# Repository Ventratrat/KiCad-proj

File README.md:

# THIS REPO IS OUTDATED AND NO LONGER UPDATED
KiCad projects I worked on
------------------------------------
# Projects in Repository
+ Test Stand - Testing stand files for PCB used to test thrust of RC aircraft.
+ 4-Bit Adder - Schematic and PCB for a simple 4-bit adder.

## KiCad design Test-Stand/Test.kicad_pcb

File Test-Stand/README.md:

# Overview
This folder contains most of, if not all, of the files used for a chip designed to test the voltage and current of an RC plane battery.

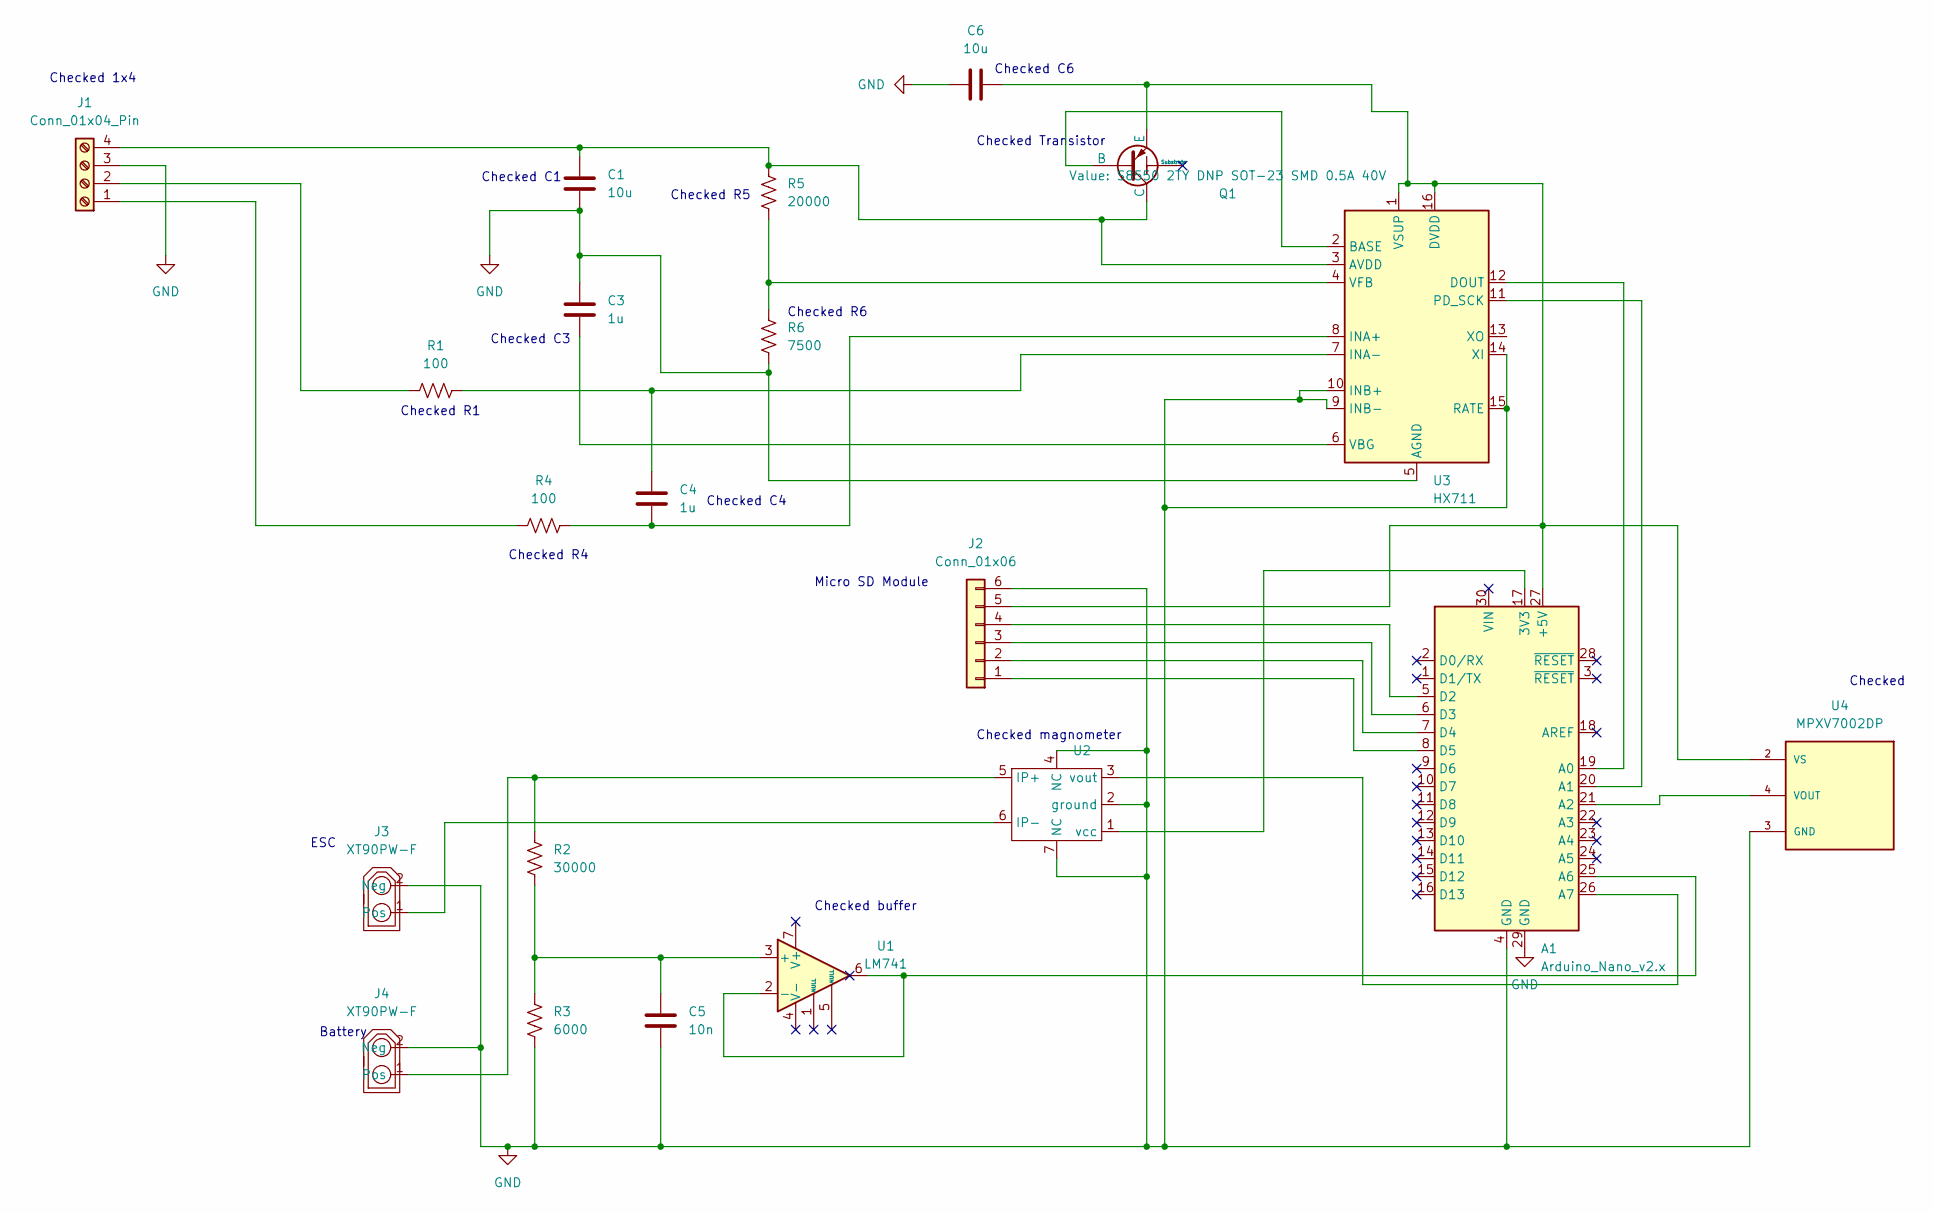
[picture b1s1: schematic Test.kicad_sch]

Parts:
A1: Arduino_Nano_v2.x; Arduino_Nano
C1, C6: 10u; Capacitor_4mm_diam_.6mm_pin
C3, C4: 1u; Capacitor_4mm_diam_.6mm_pin
C5: 10n; Capacitor_4mm_diam_.6mm_pin
J1: Conn_01x04_Pin; JST_EH_B4B-EH-A_1x04_P2.50mm_Vertical
J2: Conn_01x06; JST_EH_B6B-EH-A_1x06_P2.50mm_Vertical
J3, J4: XT90PW-F; XT90_-F; PARTREV V00
Q1: S8550 2TY DNP SOT-23 SMD 0.5A 40V; SOT-23
R1, R4: 100; R_1watt
R2: 30000; R_1watt
R3: 6000; R_1watt
R5: 20000; R_1watt
R6: 7500; R_1watt
U1: LM741; SOIC-8_W3.9mm
U2: ACS781LLRTR-100U-T
U3: HX711; SOP-16_3.9x9.9mm_P1.27mm
U4: MPXV7002DP; XDCR_MPXV7002DP; PARTREV 4

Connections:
GND: A1.4 (GND), A1.29 (GND), C1.2, C3.1, C5.2, C6.2, J1.3, J2.6, J3.2 (Neg), J4.2 (Neg), R3.2, R6.2, U2.2 (ground), U2.4 (NC), U2.7 (NC), U3.5 (AGND), U3.9 (INB-), U3.10 (INB+), U3.14 (XI), U3.15 (RATE), U4.3 (GND)
unnamed: A1.17 (3V3), U2.1 (vcc)
unnamed: A1.27 (+5V), C6.1, J2.5, Q1.3 (E), U3.1 (VSUP), U3.16 (DVDD), U4.2 (VS)
unnamed: A1.19 (A0), U3.12 (DOUT)
unnamed: A1.20 (A1), U3.11 (PD_SCK)
unnamed: A1.21 (A2), U4.4 (VOUT)
unnamed: A1.25 (A6), U1.2 (-), U1.6
unnamed: A1.26 (A7), U2.3 (vout)
unnamed: A1.5 (D2), J2.4
unnamed: A1.6 (D3), J2.3
unnamed: A1.7 (D4), J2.2
unnamed: A1.8 (D5), J2.1
unnamed: J1.1, R4.1
unnamed: J1.2, R1.1
unnamed: C1.1, J1.4, Q1.1 (C), R5.1, U3.3 (AVDD)
unnamed: J3.1 (Pos), U2.6 (IP-)
unnamed: J4.1 (Pos), R2.1, U2.5 (IP+)
unnamed: Q1.2 (B), U3.2 (BASE)
unnamed: C5.1, R2.2, R3.1, U1.3 (+)
unnamed: C4.2, R4.2, U3.8 (INA+)
unnamed: C4.1, R1.2, U3.7 (INA-)
unnamed: C3.2, U3.6 (VBG)
unnamed: R5.2, R6.1, U3.4 (VFB)

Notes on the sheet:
Checked R4
Checked R6
Checked Transistor
Checked R1
Checked C3
Checked C1
Battery
ESC
Checked R5
Micro SD Module
Checked
Checked 1x4
Checked magnometer
Checked C4
Checked buffer
Checked C6

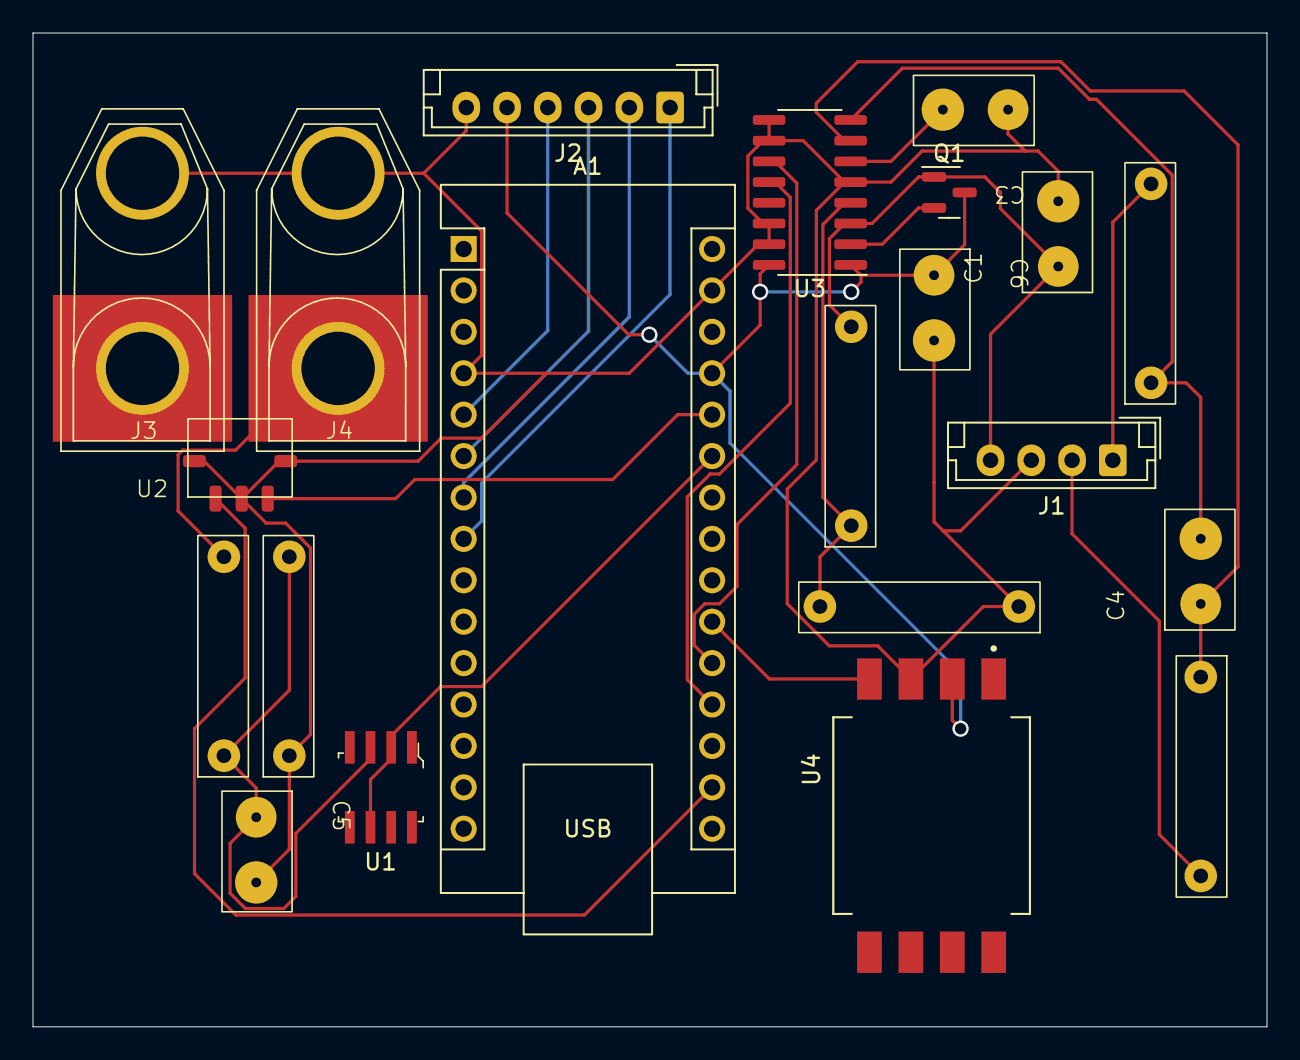
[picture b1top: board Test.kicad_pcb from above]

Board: 2 copper layers, 75.7 x 61.0 mm, 21 parts (0 on the bottom side), 23 nets.

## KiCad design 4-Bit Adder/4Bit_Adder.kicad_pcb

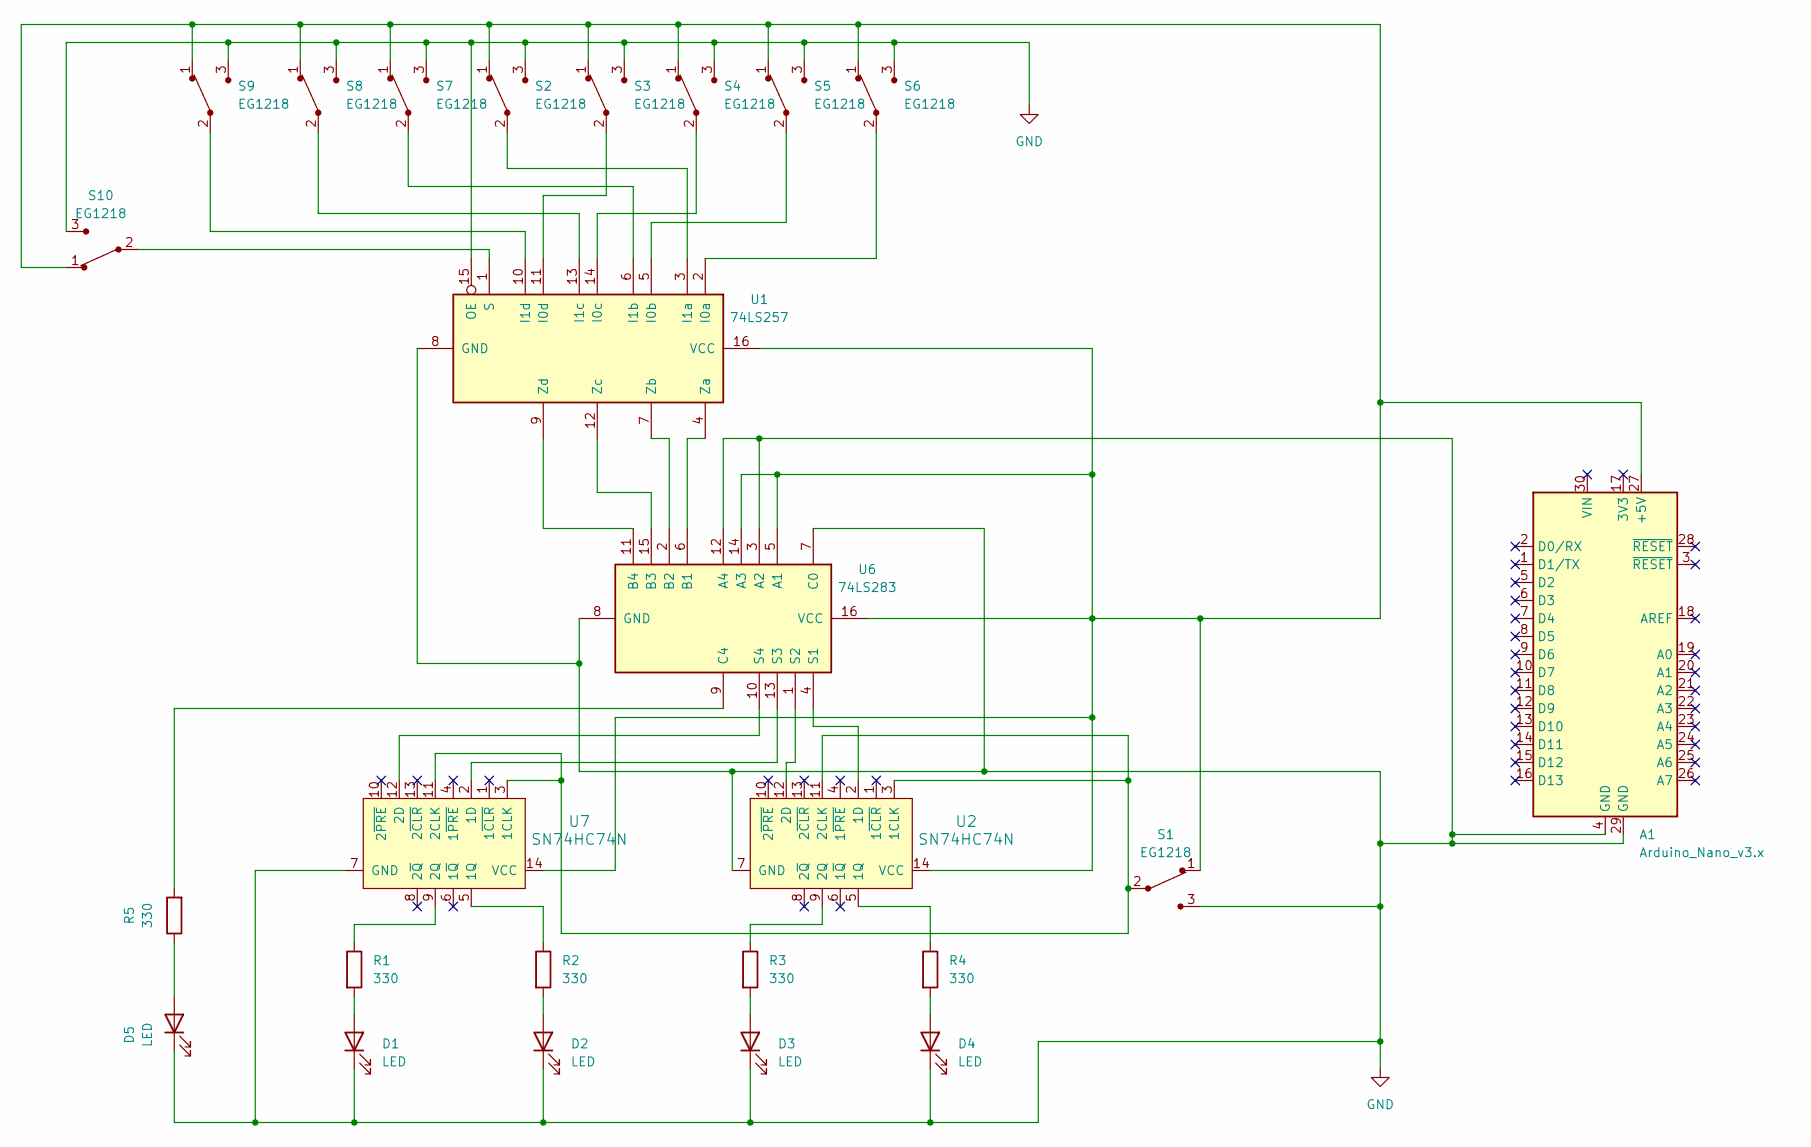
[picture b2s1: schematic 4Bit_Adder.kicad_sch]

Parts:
A1: Arduino_Nano_v3.x; Arduino_Nano
D1, D2, D3, D4, D5: LED; LED_5mm_Radial
R1, R2, R3, R4, R5: 330; R_1watt
S1: EG1218; PushButton_12x12mm_THT_GPTS203211B; MPN EG1218; Digi-Key_PN EG1903-ND
S2, S3, S4, S5, S6, S7, S8, S9, S10: EG1218; Switch_Slide_11.6x4mm_EG1218; MPN EG1218; Digi-Key_PN EG1903-ND
U1: 74LS257; SOIC-16_W7.5mm
U2, U7: SN74HC74N; DIP-14_W3mm; MPN SN74HC74N; Digi-Key_PN 296-1602-5-ND
U6: 74LS283; DIP-16_W10.16mm

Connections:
GND: A1.4 (GND), A1.29 (GND), D1.1 (K), D2.1 (K), D3.1 (K), D4.1 (K), D5.1 (K), S1.3, S2.3, S3.3, S4.3, S5.3, S6.3, S7.3, S8.3, S9.3, S10.3, U1.8 (GND), U1.15 (OE), U2.7 (GND), U6.3 (A2), U6.7 (C0), U6.8 (GND), U6.12 (A4), U7.7 (GND)
unnamed: A1.27 (+5V), S1.1, S2.1, S3.1, S4.1, S5.1, S6.1, S7.1, S8.1, S9.1, S10.1, U1.16 (VCC), U2.14 (VCC), U6.5 (A1), U6.14 (A3), U6.16 (VCC), U7.14 (VCC)
unnamed: D1.2 (A), R1.2
unnamed: D2.2 (A), R2.2
unnamed: D3.2 (A), R3.2
unnamed: D4.2 (A), R4.2
unnamed: D5.2 (A), R5.1
unnamed: S6.2, U1.2 (I0a)
unnamed: S5.2, U1.5 (I0b)
unnamed: S4.2, U1.14 (I0c)
unnamed: S3.2, U1.11 (I0d)
unnamed: S2.2, U1.3 (I1a)
unnamed: S7.2, U1.6 (I1b)
unnamed: S8.2, U1.13 (I1c)
unnamed: S9.2, U1.10 (I1d)
unnamed: S10.2, U1.1 (S)
unnamed: U1.4 (Za), U6.6 (B1)
unnamed: U1.7 (Zb), U6.2 (B2)
unnamed: U1.12 (Zc), U6.15 (B3)
unnamed: U1.9 (Zd), U6.11 (B4)
unnamed: S1.2, U2.3 (1CLK), U2.11 (2CLK), U7.3 (1CLK), U7.11 (2CLK)
unnamed: U2.2 (1D), U6.4 (S1)
unnamed: R4.1, U2.5 (1Q)
unnamed: U2.12 (2D), U6.1 (S2)
unnamed: R3.1, U2.9 (2Q)
unnamed: R5.2, U6.9 (C4)
unnamed: U6.13 (S3), U7.2 (1D)
unnamed: U6.10 (S4), U7.12 (2D)
unnamed: R2.1, U7.5 (1Q)
unnamed: R1.1, U7.9 (2Q)

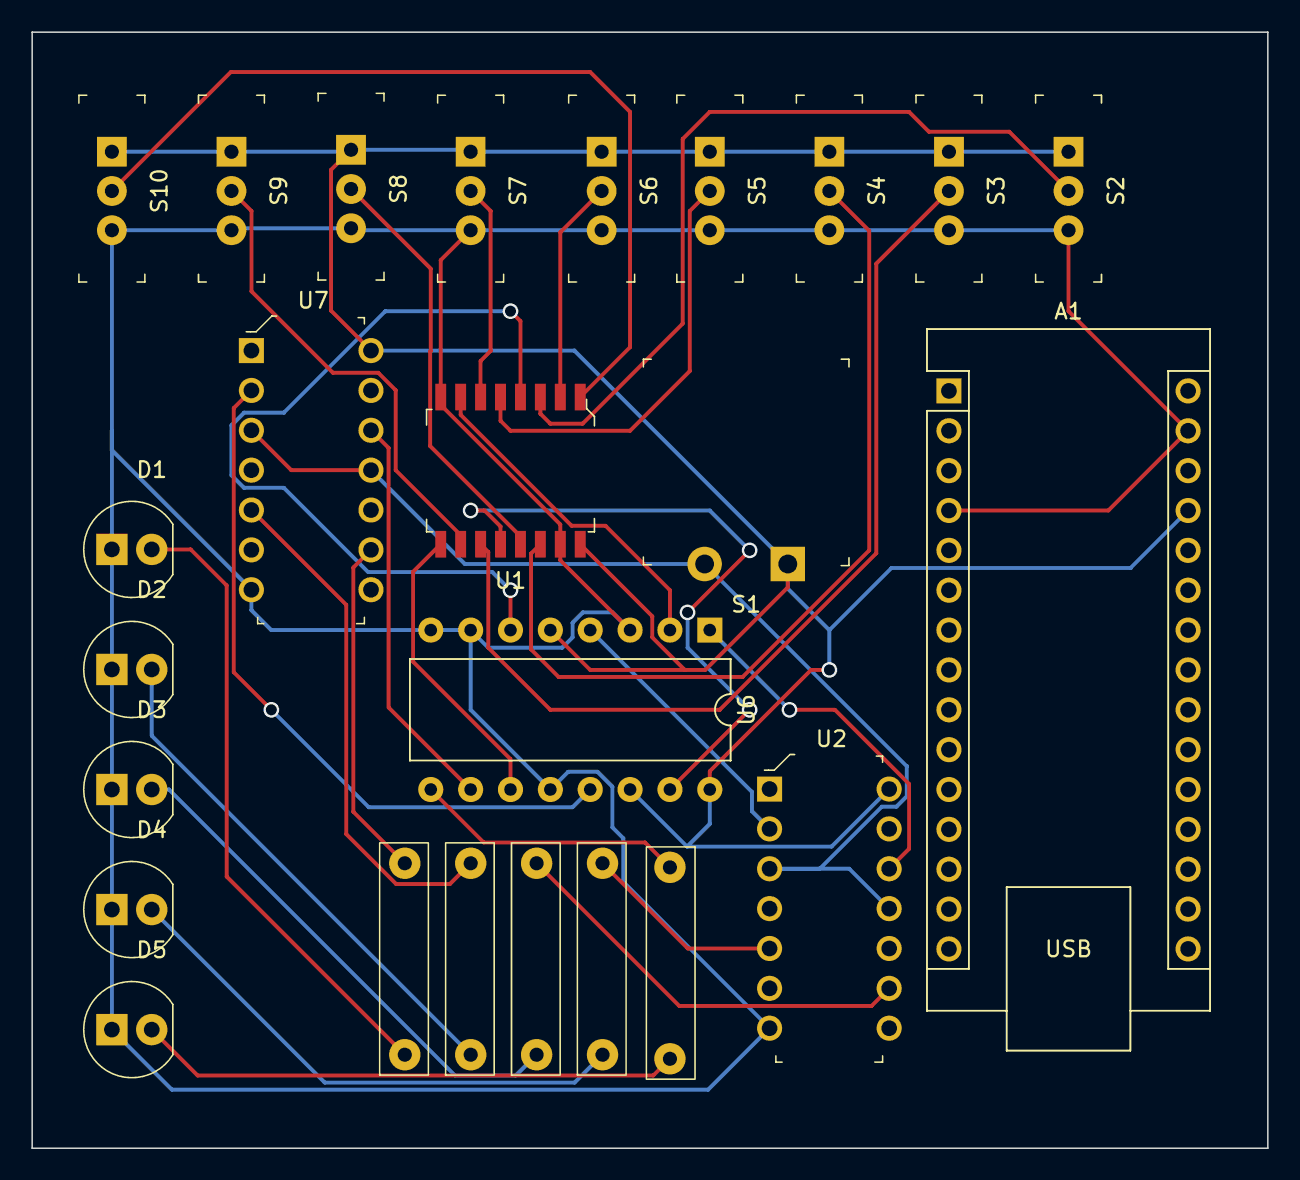
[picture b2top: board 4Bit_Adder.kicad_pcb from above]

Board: 2 copper layers, 78.7 x 71.1 mm, 25 parts (0 on the bottom side), 30 nets.

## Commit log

2023-10-11 Added symbol and footprint for ACS781
2023-10-27 Added updated ACS781 footprint
2023-10-27 Uploaded updated schematic for test stand
2023-10-27 Updated symbol for acs781xlr
2023-10-27 Attempt at 4-bit adder (no power source :c )
2023-10-27 Added project and pcb files
2023-10-30 Create placeholder
2023-10-30 Added 4-bit adder files
2023-11-10 Updated project files
2023-11-15 Updated test stand files
